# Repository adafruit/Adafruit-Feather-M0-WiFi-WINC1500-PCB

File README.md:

# Adafruit-Feather-M0-WiFi-WINC1500-PCB
PCB files for the Adafruit Feather M0 WiFi (with WINC1500) PCB

Format is EagleCAD schematic and board layout

For more details, check out the product page at

  * https://www.adafruit.com/product/3010

Adafruit invests time and resources providing this open source design, 
please support Adafruit and open-source hardware by purchasing 
products from Adafruit!

Designed by Adafruit Industries.  
Creative Commons Attribution, Share-Alike license, check license.txt for more information
All text above must be included in any redistribution

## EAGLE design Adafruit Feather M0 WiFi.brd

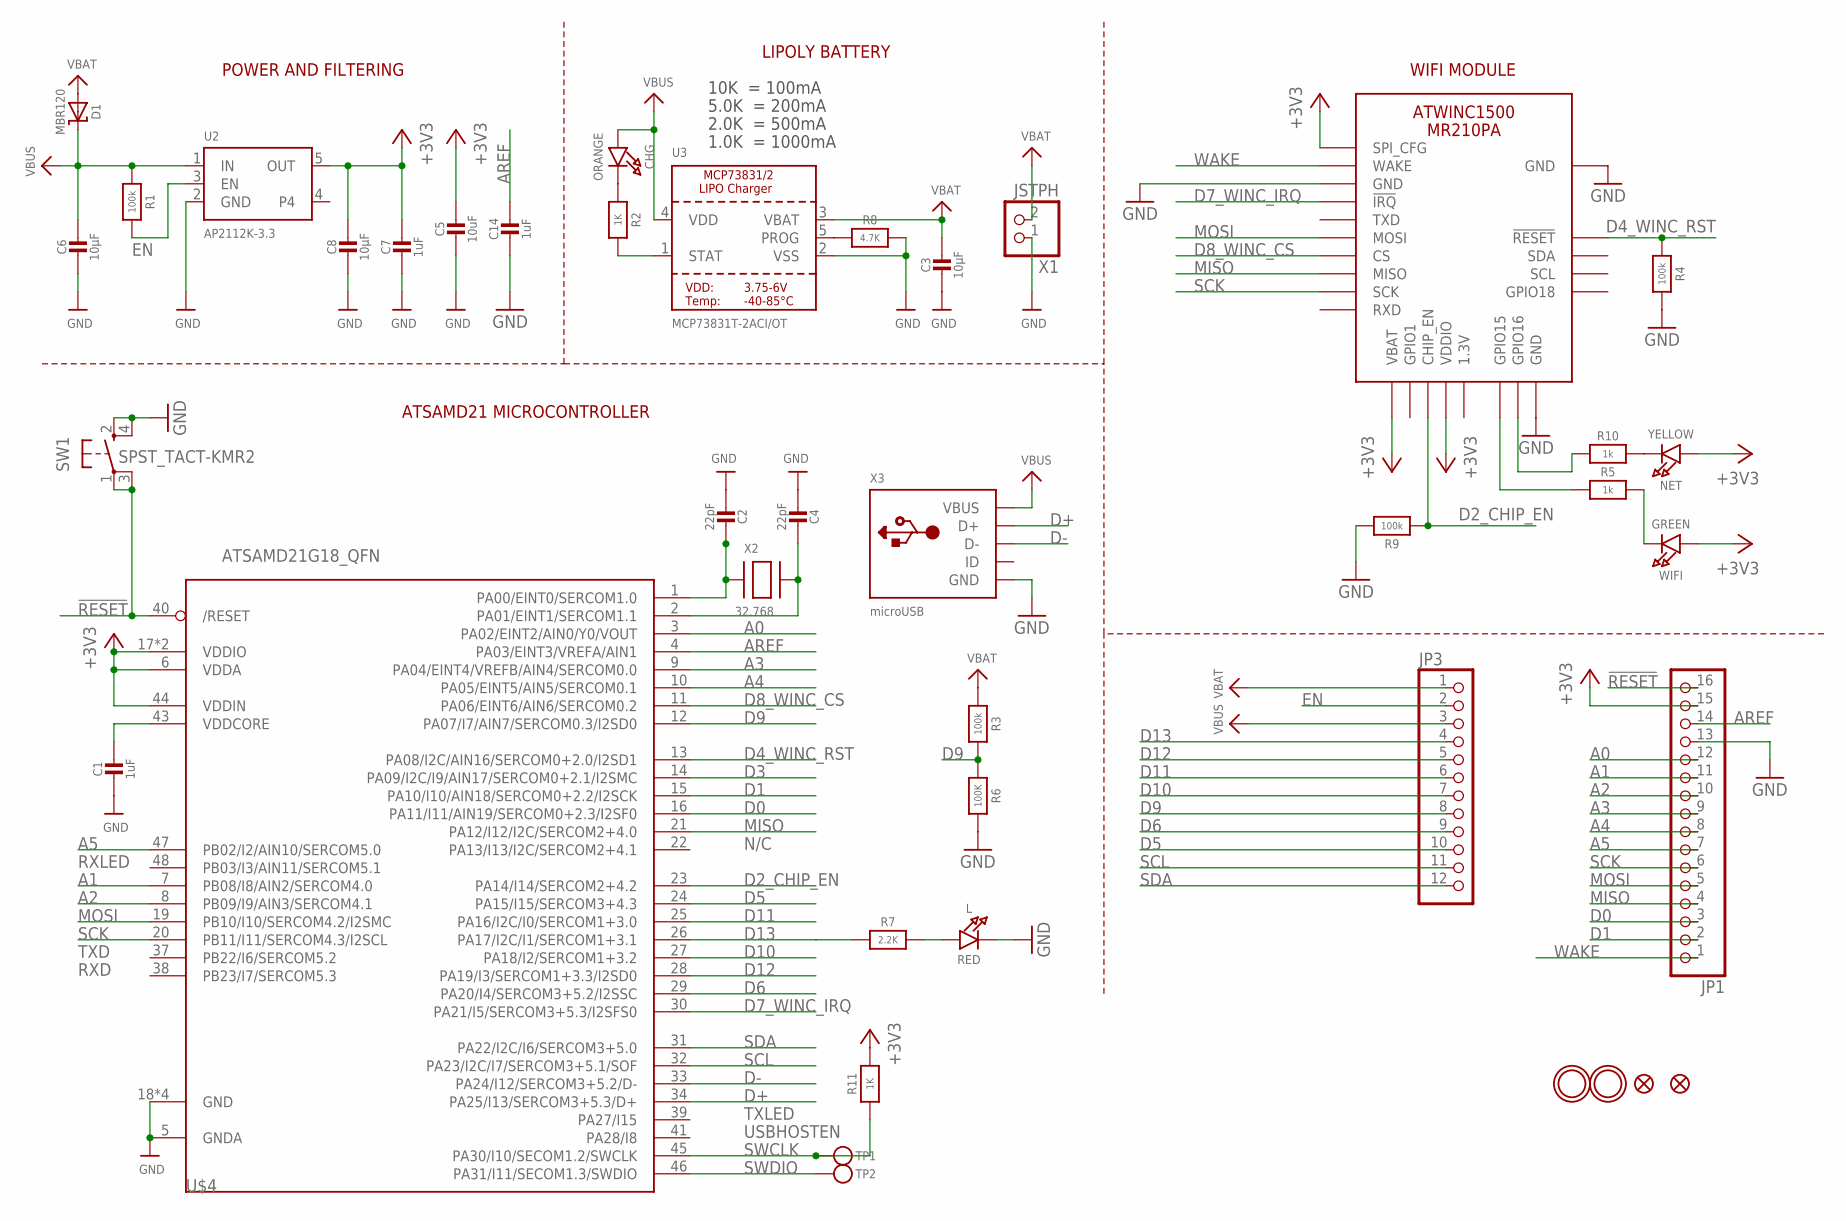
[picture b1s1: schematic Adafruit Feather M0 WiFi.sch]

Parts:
C1, C7, C14: 1uF; 0603-NO
C2, C4: 22pF; 0603-NO
C3, C6, C8: 10µF; 0805-NO
C5: 10uF; 0805-NO
CHG: ORANGE; CHIPLED_0805_NOOUTLINE
D1: MBR120; SOD-123
JP1: HEADER-1X16ROUND; 1X16_ROUND
JP3: HEADER-1X12; 1X12_ROUND
L: RED; CHIPLED_0805_NOOUTLINE
NET: YELLOW; CHIPLED_0805_NOOUTLINE
R1, R3, R4, R9: 100k; 0603-NO
R2, R11: 1K; 0603-NO
R5, R10: 1k; 0603-NO
R6: 100K; 0603-NO
R7: 2.2K; 0603-NO
R8: 4.7K; 0603-NO
SW1: SPST_TACT-KMR2; KMR2
TP1, TP2: TESTPOINTROUND1.5MM; TESTPOINT_ROUND_1.5MM
U2: AP2112K-3.3; SOT23-5
U3: MCP73831T-2ACI/OT; SOT23-5
U$4: ATSAMD21G18_QFN; TQFN48_7MM
U$31, U$32: MOUNTINGHOLE2.5; MOUNTINGHOLE_2.5_PLATED
U$34, U$35: FIDUCIAL""; FIDUCIAL_1MM
WIFI: GREEN; CHIPLED_0805_NOOUTLINE
X1: JSTPH; JSTPH2
X2: 32.768; XTAL3215
X3: microUSB; 4UCONN_20329_V2
X4: ATWINC1500_MR210PA

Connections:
!RESET: JP1.16, SW1.1, SW1.3 (P1), U$4.40 (/RESET)
+3V3: C5.1, C7.1, C8.1, JP1.15, NET.A, R11.2, U2.5 (OUT), U$4.6 (VDDA), U$4.17 (VDDIO), U$4.36 (VDDIO), U$4.44 (VDDIN), WIFI.A, X4.J10 (SPI_CFG), X4.J20 (VBAT), X4.J23 (VDDIO)
A0: JP1.12, U$4.3 (PA02/EINT2/AIN0/Y0/VOUT)
A1: JP1.11, U$4.7 (PB08/I8/AIN2/SERCOM4.0)
A2: JP1.10, U$4.8 (PB09/I9/AIN3/SERCOM4.1)
A3: JP1.9, U$4.9 (PA04/EINT4/VREFB/AIN4/SERCOM0.0)
A4: JP1.8, U$4.10 (PA05/EINT5/AIN5/SERCOM0.1)
A5: JP1.7, U$4.47 (PB02/I2/AIN10/SERCOM5.0)
AREF: C14.1, JP1.14, U$4.4 (PA03/EINT3/VREFA/AIN1)
D0: JP1.3, U$4.16 (PA11/I11/AIN19/SERCOM0+2.3/I2SF0)
D1: JP1.2, U$4.15 (PA10/I10/AIN18/SERCOM0+2.2/I2SCK)
D2_CHIP_EN: R9.1, U$4.23 (PA14/I14/SERCOM2+4.2), X4.J22 (CHIP_EN)
D3: U$4.14 (PA09/I2C/I9/AIN17/SERCOM0+2.1/I2SMC)
D4_WINC_RST: R4.1, U$4.13 (PA08/I2C/AIN16/SERCOM0+2.0/I2SD1), X4.J4 (!RESET)
D5: JP3.10, U$4.24 (PA15/I15/SERCOM3+4.3)
D6: JP3.9, U$4.29 (PA20/I4/SERCOM3+5.2/I2SSC)
D7_WINC_IRQ: U$4.30 (PA21/I5/SERCOM3+5.3/I2SFS0), X4.J13 (!IRQ)
D8_WINC_CS: U$4.11 (PA06/EINT6/AIN6/SERCOM0.2), X4.J16 (CS)
D9: JP3.8, R3.2, R6.1, U$4.12 (PA07/I7/AIN7/SERCOM0.3/I2SD0)
D10: JP3.7, U$4.27 (PA18/I2/SERCOM1+3.2)
D11: JP3.6, U$4.25 (PA16/I2C/I0/SERCOM1+3.0)
D12: JP3.5, U$4.28 (PA19/I3/SERCOM1+3.3/I2SD0)
D13: JP3.4, R7.1, U$4.26 (PA17/I2C/I1/SERCOM1+3.1)
D+: U$4.34 (PA25/I13/SERCOM3+5.3/D+), X3.D+
D-: U$4.33 (PA24/I12/SERCOM3+5.2/D-), X3.D-
EN: JP3.2, R1.2, U2.3 (EN)
GND: C1.2, C2.2, C3.2, C4.2, C5.2, C6.2, C7.2, C8.2, C14.2, JP1.13, L.C, R4.2, R6.2, R8.2, R9.2, SW1.2 (S), SW1.4 (S1), U2.2 (GND), U3.2 (VSS), U$4.5 (GNDA), U$4.18 (GND), U$4.35 (GND), U$4.42 (GND), U$4.THERMAL (GND), X1.1, X3.BASE@1 (GND), X3.BASE@2 (GND), X3.GND, X3.SPRT@1 (GND), X3.SPRT@2 (GND), X3.SPRT@3 (GND), X3.SPRT@4 (GND), X4.J9 (GND), X4.J12 (GND), X4.J28 (GND), X4.MTGND (GND)
MISO: JP1.4, U$4.21 (PA12/I12/I2C/SERCOM2+4.0), X4.J17 (MISO)
MOSI: JP1.5, U$4.19 (PB10/I10/SERCOM4.2/I2SMC), X4.J15 (MOSI)
unnamed: CHG.C, R2.1
unnamed: L.A, R7.2
unnamed: R2.2, U3.1 (STAT)
unnamed: R8.1, U3.5 (PROG)
unnamed: C2.1, U$4.1 (PA00/EINT0/SERCOM1.0), X2.P$1
unnamed: R5.1, X4.J26 (GPIO15)
unnamed: C4.1, U$4.2 (PA01/EINT1/SERCOM1.1), X2.P$2
unnamed: R10.1, X4.J27 (GPIO16)
unnamed: R5.2, WIFI.C
unnamed: NET.C, R10.2
SCK: JP1.6, U$4.20 (PB11/I11/SERCOM4.3/I2SCL), X4.J18 (SCK)
SCL: JP3.11, U$4.32 (PA23/I2C/I7/SERCOM3+5.1/SOF)
SDA: JP3.12, U$4.31 (PA22/I2C/I6/SERCOM3+5.0)
SWCLK: R11.1, TP1.P$1, U$4.45 (PA30/I10/SECOM1.2/SWCLK)
SWDIO: TP2.P$1, U$4.46 (PA31/I11/SECOM1.3/SWDIO)
VBAT: C3.1, D1.A, JP3.1, R3.1, U3.3 (VBAT), X1.2
VBUS: C6.1, CHG.A, D1.C, JP3.3, R1.1, U2.1 (IN), U3.4 (VDD), X3.VBUS
VDDCORE: C1.1, U$4.43 (VDDCORE)
WAKE: JP1.1, X4.J11 (WAKE)

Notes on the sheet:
POWER AND FILTERING
10K = 100mA
5.0K = 200mA
2.0K = 500mA
1.0K = 1000mA
N/C
TXLED
USBHOSTEN
RXLED
TXD
RXD
LIPOLY BATTERY
WIFI MODULE
ATSAMD21 MICROCONTROLLER

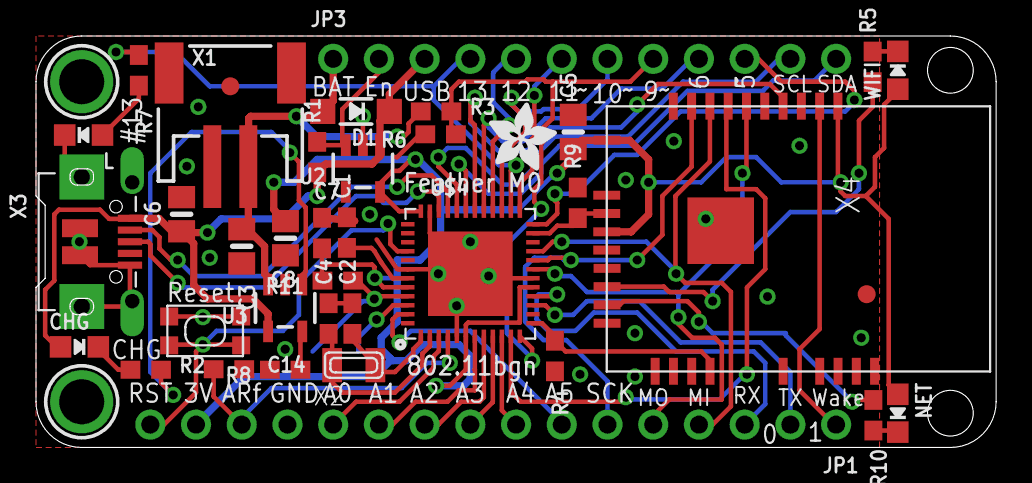
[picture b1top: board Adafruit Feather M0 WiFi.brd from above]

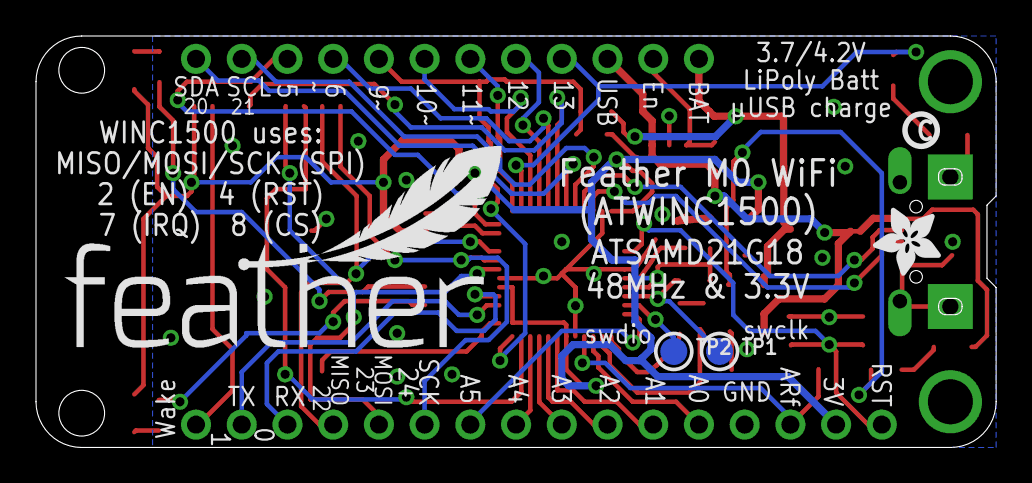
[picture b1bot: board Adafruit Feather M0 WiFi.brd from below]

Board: 2 copper layers, 53.3 x 22.9 mm, 45 parts (5 on the bottom side), 47 nets.

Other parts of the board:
U$7, U$12: ADAFRUIT_3.5MM
U$9: FEATHERLOGO
U$13: PCBFEAT-REV-040

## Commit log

2016-03-01 init
2019-05-15 Deleting brd file
2019-05-15 Deleting sch file
2019-05-15 Updating files.
2022-04-19 Added PrettyPins

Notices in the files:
parts and their libraries:
microbuilder: This work is placed in the public domain, and may be freely used for commercial and non-commercial work with the following conditions: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
